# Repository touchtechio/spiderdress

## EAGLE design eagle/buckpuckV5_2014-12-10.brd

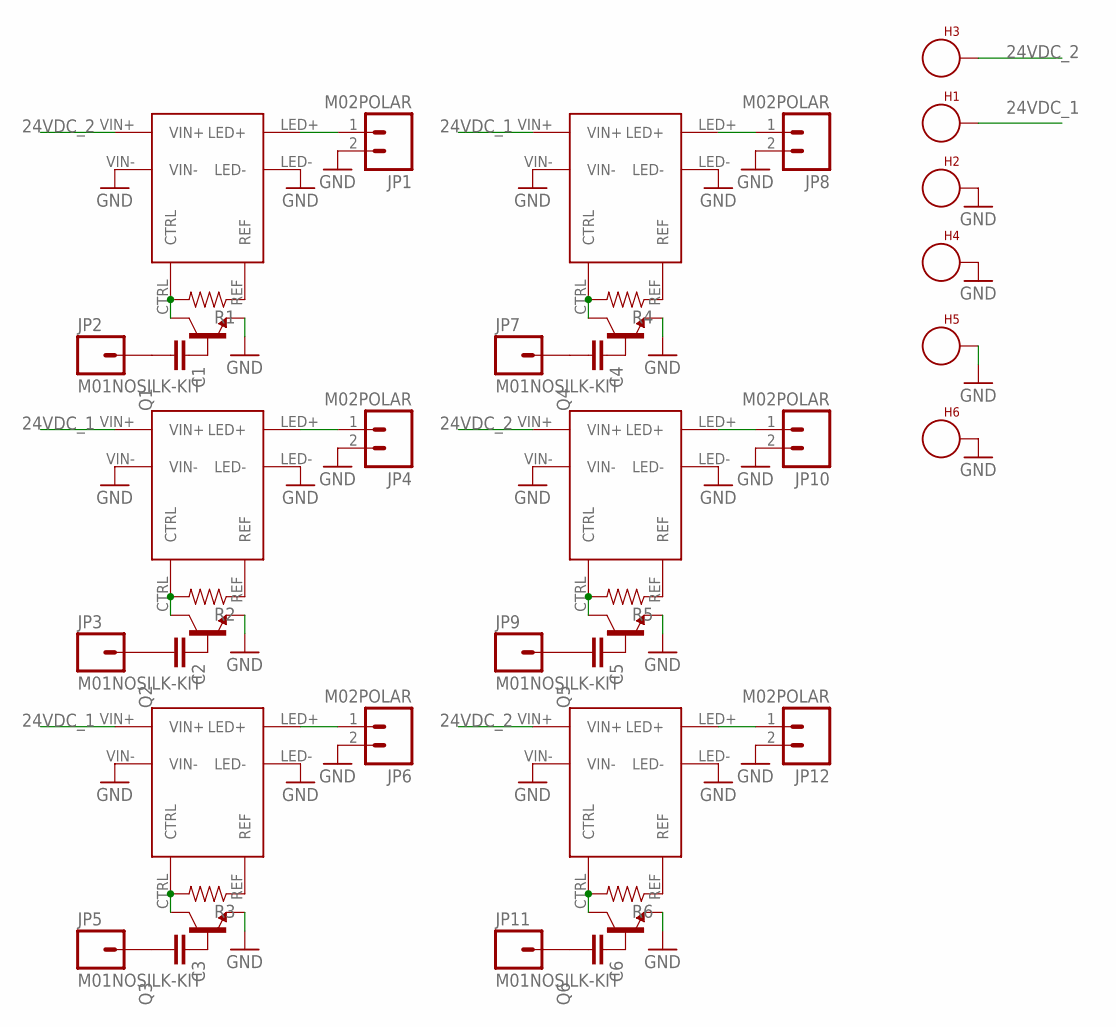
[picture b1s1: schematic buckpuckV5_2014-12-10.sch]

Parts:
C1, C2, C3, C4, C5, C6: CAPEZ; CAP-PTH-SMALLEZ
H1, H2, H3, H4, H5, H6: SEW_HOLE; SIMPLE_HOLE
JP1, JP4, JP6, JP8, JP10, JP12: M02POLAR; MOLEX-1X2
JP2, JP3, JP5, JP7, JP9, JP11: M01NOSILK-KIT; 1X01NS-KIT
Q1, Q2, Q3, Q4, Q5, Q6: TRANSISTOR_BJT_NPN-TO-92-EBC; TO-92
R1, R2, R3, R4, R5, R6: RESISTOREZ; AXIAL-0.3EZ
U$1, U$2, U$3, U$4, U$5, U$6: BUCKPUCK

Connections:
24VDC_1: H1.P$1, U$2.VIN+, U$3.VIN+, U$4.VIN+
24VDC_2: H3.P$1, U$1.VIN+, U$5.VIN+, U$6.VIN+
GND: H2.P$1, H4.P$1, H5.P$1, H6.P$1, JP1.2, JP4.2, JP6.2, JP8.2, JP10.2, JP12.2, Q1.1 (E), Q2.1 (E), Q3.1 (E), Q4.1 (E), Q5.1 (E), Q6.1 (E), U$1.LED-, U$1.VIN-, U$2.LED-, U$2.VIN-, U$3.LED-, U$3.VIN-, U$4.LED-, U$4.VIN-, U$5.LED-, U$5.VIN-, U$6.LED-, U$6.VIN-
unnamed: R1.P$1 (1), U$1.REF
unnamed: Q1.3 (C), R1.P$2 (2), U$1.CTRL
unnamed: C1.1, Q1.2 (B)
unnamed: R4.P$1 (1), U$4.REF
unnamed: JP1.1, U$1.LED+
unnamed: C1.2, JP2.1
unnamed: C2.1, Q2.2 (B)
unnamed: Q2.3 (C), R2.P$2 (2), U$2.CTRL
unnamed: C4.1, Q4.2 (B)
unnamed: C3.1, Q3.2 (B)
unnamed: JP4.1, U$2.LED+
unnamed: C2.2, JP3.1
unnamed: C6.1, Q6.2 (B)
unnamed: Q3.3 (C), R3.P$2 (2), U$3.CTRL
unnamed: Q4.3 (C), R4.P$2 (2), U$4.CTRL
unnamed: JP6.1, U$3.LED+
unnamed: C3.2, JP5.1
unnamed: R2.P$1 (1), U$2.REF
unnamed: C5.1, Q5.2 (B)
unnamed: R5.P$1 (1), U$5.REF
unnamed: R3.P$1 (1), U$3.REF
unnamed: JP8.1, U$4.LED+
unnamed: C4.2, JP7.1
unnamed: R6.P$1 (1), U$6.REF
unnamed: Q5.3 (C), R5.P$2 (2), U$5.CTRL
unnamed: JP10.1, U$5.LED+
unnamed: C5.2, JP9.1
unnamed: Q6.3 (C), R6.P$2 (2), U$6.CTRL
unnamed: JP12.1, U$6.LED+
unnamed: C6.2, JP11.1

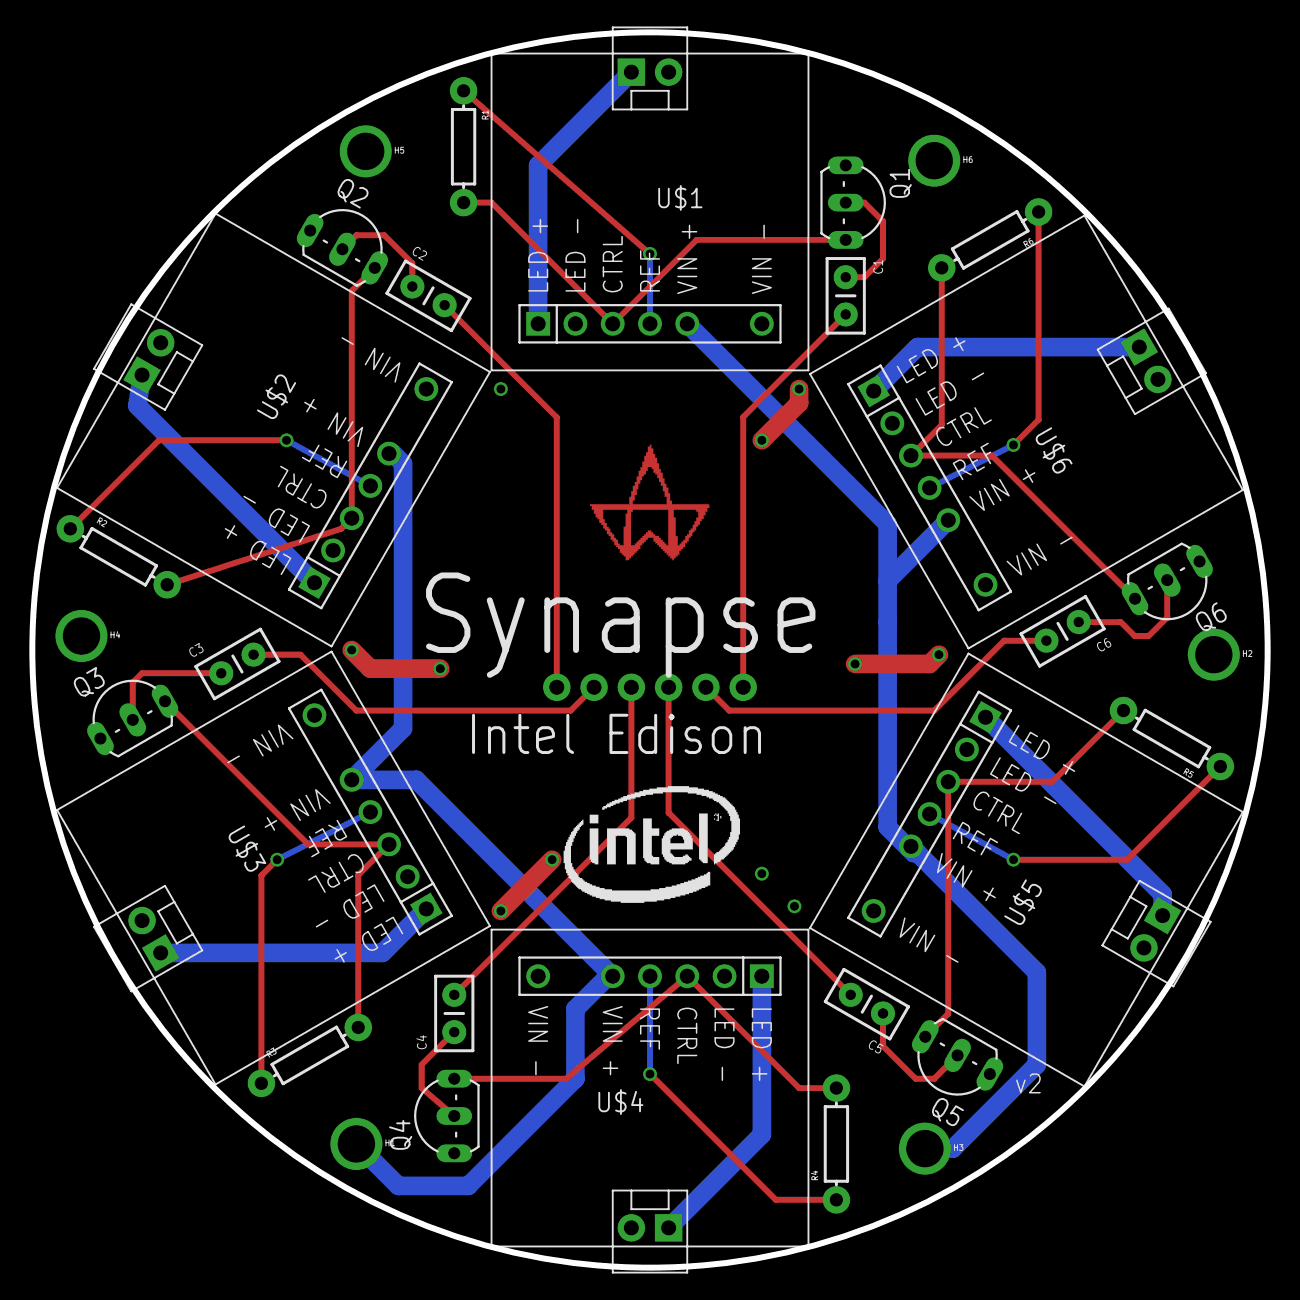
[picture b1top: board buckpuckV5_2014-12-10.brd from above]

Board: 2 copper layers, 84.2 x 84.2 mm, 44 parts (1 on the bottom side), 33 nets.

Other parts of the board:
U$7: NOUKLOGO3IN
U$8: NOUKLOGO300MIL_COPPER

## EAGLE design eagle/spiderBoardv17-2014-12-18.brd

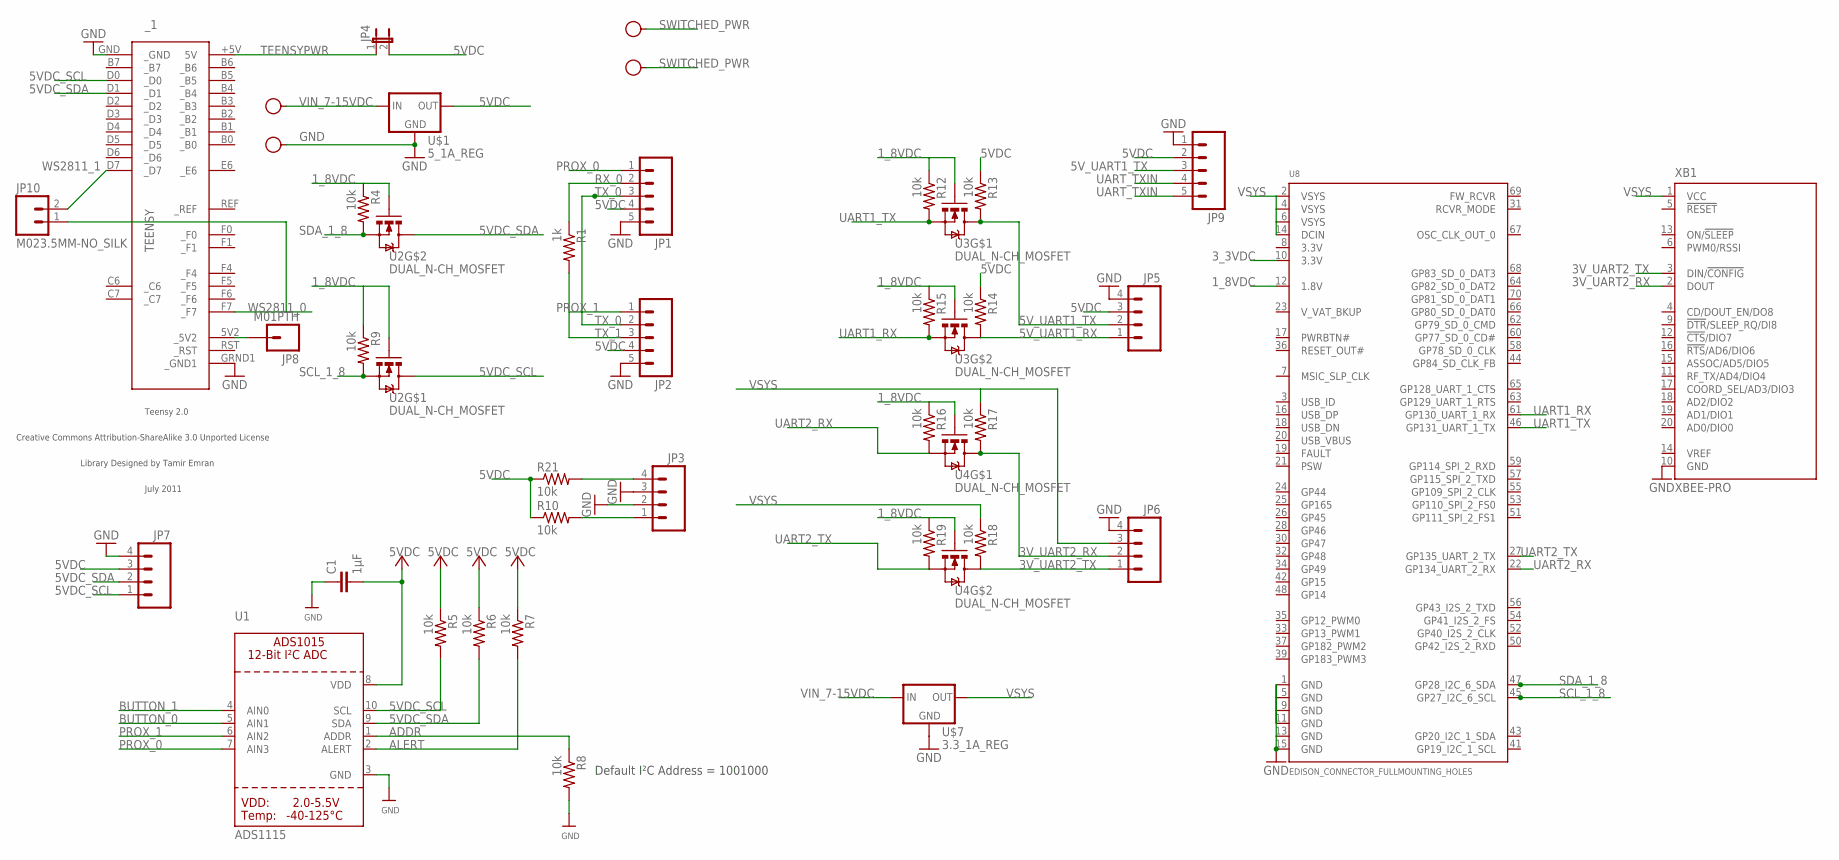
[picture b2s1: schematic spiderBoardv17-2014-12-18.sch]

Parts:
C1: 1µF; 0603-CAP
GND, GND15: SEW_HOLE-SMALL; SIMPLE_HOLE_SM
JP1, JP2, JP9: M05PTH; 1X05
JP3, JP5, JP6, JP7: M04PTH; 1X04
JP4: JUMPER-2SMD-NC; SJ_2S
JP8: M01PTH; 1X01
JP10: M023.5MM-NO_SILK; SCREWTERMINAL-3.5MM-2-NS
R1: 1k; 0603-RES
R4, R5, R6, R7, R8, R9, R10, R12, R13, R14, R15, R16, R17, R18, R19, R21: 10k; 0603-RES
U1: ADS1115; MSOP10
U2, U3, U4: DUAL_N-CH_MOSFET; SOT363_DUAL_N_MOSFET
U8: EDISON_CONNECTOR_FULLMOUNTING_HOLES; EDISON_DAUGHTER
U$1: 5_1A_REG; 1A_REG
U$7: 3.3_1A_REG; 1A_REG
VIN_7-15VDC, VIN_7-15VDC1: SEW_HOLE-SMALL; SIMPLE_HOLE_SM
XB1: XBEE-PRO
_1: TEENSY

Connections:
1_8VDC: R4.1, R9.1, R12.1, R15.1, R16.1, R19.1, U2.2 (G), U2.5 (G), U3.2 (G), U3.5 (G), U4.2 (G), U4.5 (G), U8.12 (1.8V)
3V_UART2_RX: JP6.2, R17.2, U4.3 (D), XB1.2 (DOUT)
3V_UART2_TX: JP6.1, R18.2, U4.6 (D), XB1.3 (DIN/!CONFIG)
3_3VDC: U8.10 (3.3V)
5VDC: C1.2, JP1.4, JP2.4, JP4.2, JP5.3, JP7.3, JP9.2, R5.1, R6.1, R7.1, R10.1, R13.1, R14.1, R21.1, U1.8 (VDD), U$1.OUT
5VDC_SCL: JP7.1, R5.2, U1.10 (SCL), U2.3 (D), _1.D0 (_D0)
5VDC_SDA: JP7.2, R6.2, U1.9 (SDA), U2.6 (D), _1.D1 (_D1)
5V_UART1_RX: JP5.1, R14.2, U3.6 (D)
5V_UART1_TX: JP5.2, JP9.3, R13.2, U3.3 (D)
ADDR: R8.1, U1.1 (ADDR)
ALERT: R7.2, U1.2 (ALERT)
BUTTON_0: JP3.4, R21.2, U1.5 (AIN1)
BUTTON_1: JP3.1, R10.2, U1.4 (AIN0)
GND: C1.1, GND.P$1, JP1.5, JP2.5, JP3.2, JP3.3, JP5.4, JP6.4, JP7.4, JP9.1, R8.2, U1.3 (GND), U8.1 (GND), U8.5 (GND), U8.9 (GND), U8.11 (GND), U8.13 (GND), U8.15 (GND), U$1.GND, U$7.GND, XB1.10 (GND), _1.GND (_GND), _1.GRND1 (_GND1)
PROX_0: JP1.1, U1.7 (AIN3)
PROX_1: JP2.1, U1.6 (AIN2)
RX_0: JP1.2, R1.1
SCL_1_8: R9.2, U2.4 (S), U8.45 (GP27_I2C_6_SCL)
SDA_1_8: R4.2, U2.1 (S), U8.47 (GP28_I2C_6_SDA)
SWITCHED_PWR: GND15.P$1, VIN_7-15VDC1.P$1
TEENSYPWR: JP4.1, JP8.1, _1.5V2 (_5V2), _1.+5V (5V)
TX_0: JP1.3, JP2.2
TX_1: JP2.3, R1.2
UART1_RX: R15.2, U3.1 (S), U8.61 (GP130_UART_1_RX)
UART1_TX: R12.2, U3.4 (S), U8.46 (GP131_UART_1_TX)
UART2_RX: R16.2, U4.4 (S), U8.22 (GP134_UART_2_RX)
UART2_TX: R19.2, U4.1 (S), U8.27 (GP135_UART_2_TX)
UART_TXIN: JP9.4, JP9.5
VIN_7-15VDC: U$1.IN, U$7.IN, VIN_7-15VDC.P$1
VSYS: JP6.3, R17.1, R18.1, U8.2 (VSYS), U8.4 (VSYS), U8.6 (VSYS), U8.14 (DCIN), U$7.OUT, XB1.1 (VCC)
WS2811_0: JP10.1, _1.F7 (_F7)
WS2811_1: JP10.2, _1.D7 (_D7)

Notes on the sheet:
Default I²C Address = 1001000

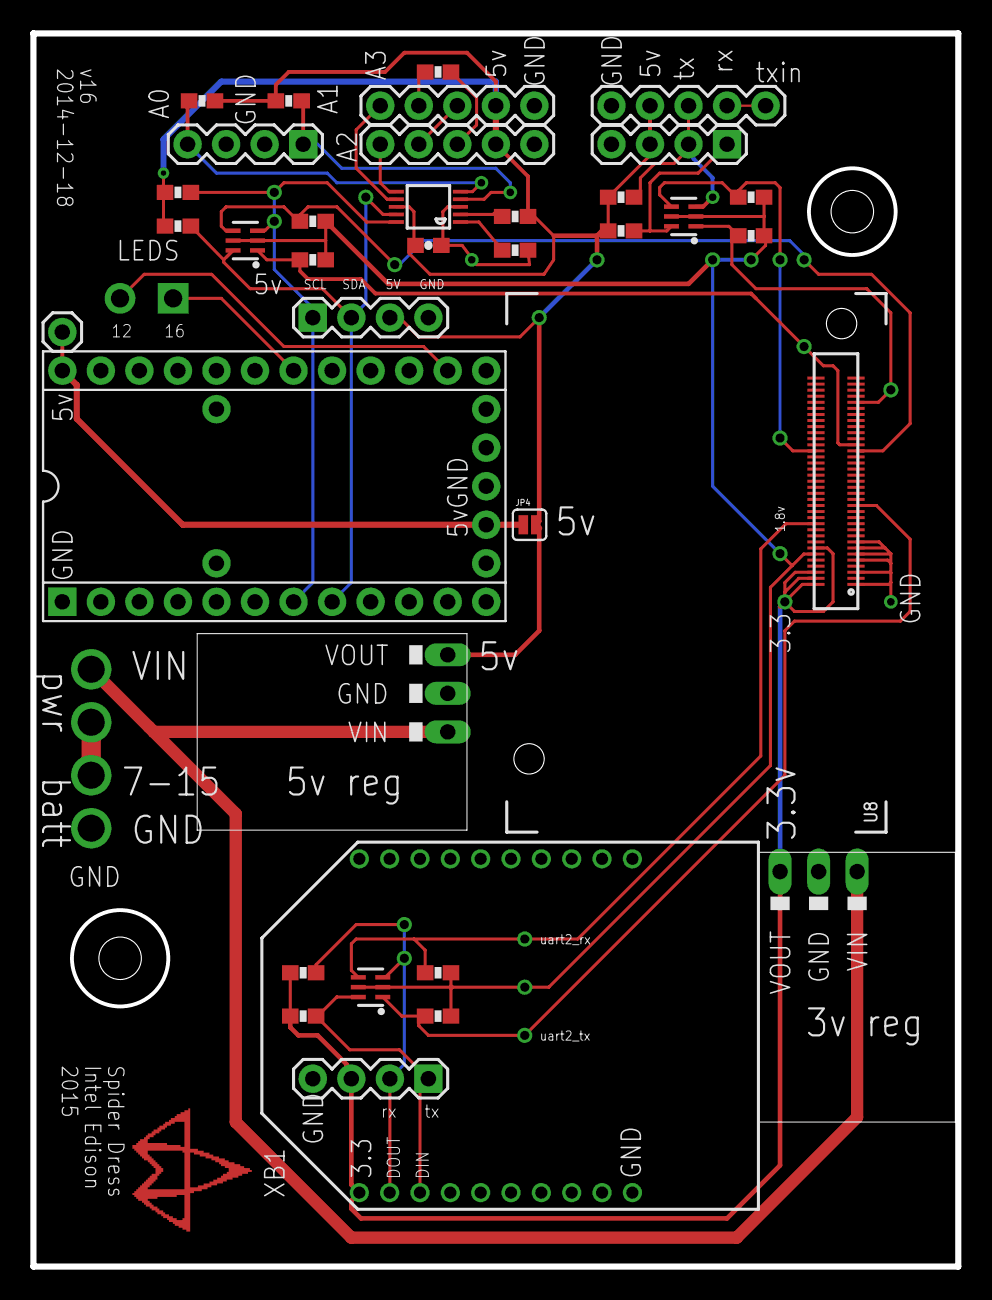
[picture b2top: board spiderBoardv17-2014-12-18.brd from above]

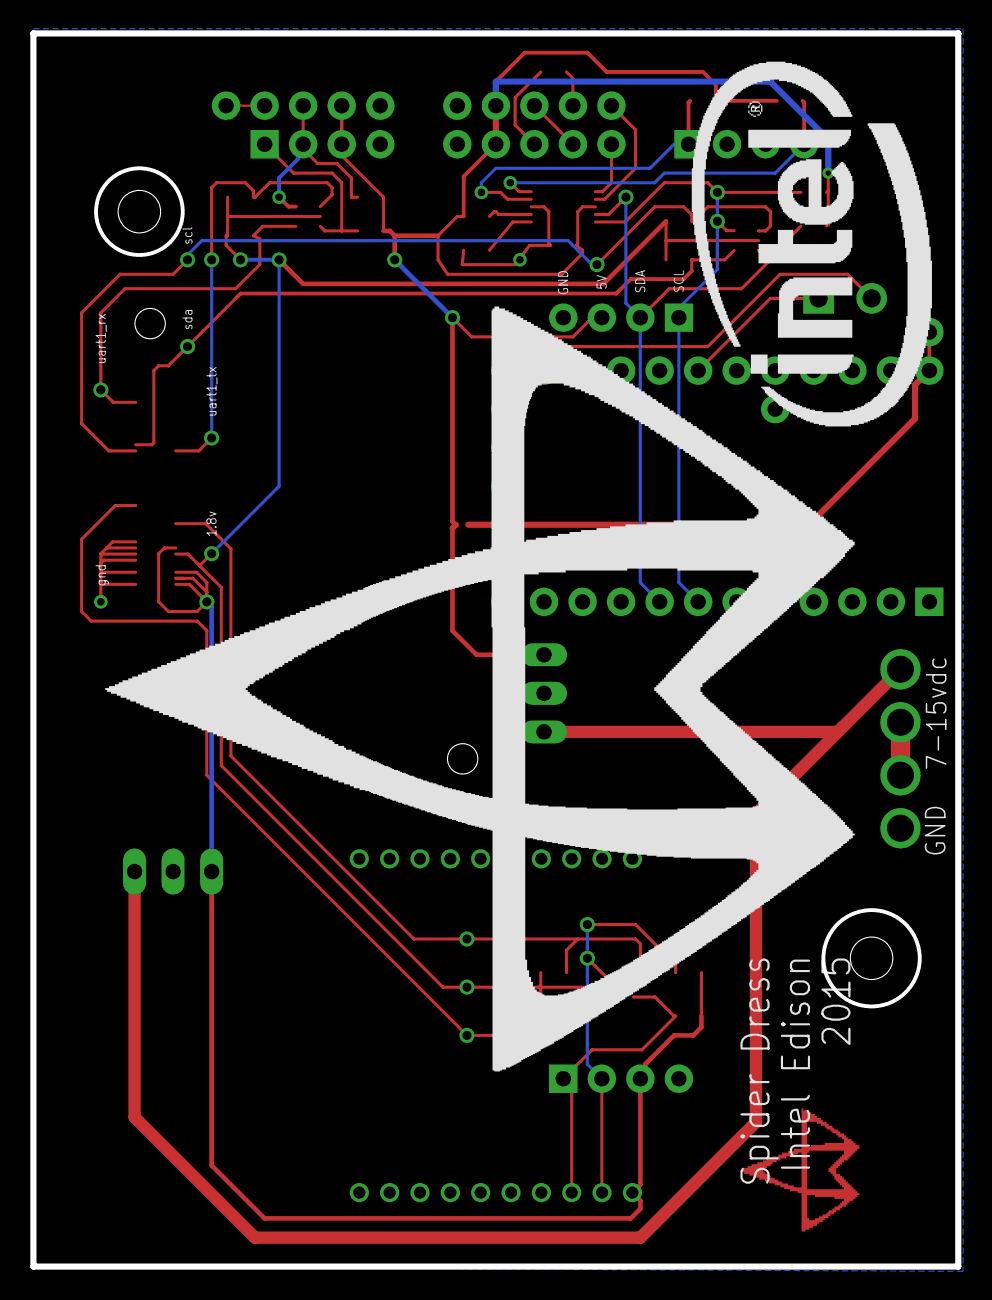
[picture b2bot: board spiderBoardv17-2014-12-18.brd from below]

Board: 2 copper layers, 61.0 x 81.3 mm, 44 parts (2 on the bottom side), 31 nets.

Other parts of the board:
U$9: NOUK-800
U$11: NOUKLOGO300MIL_COPPER
U$12: INTEL_1IN

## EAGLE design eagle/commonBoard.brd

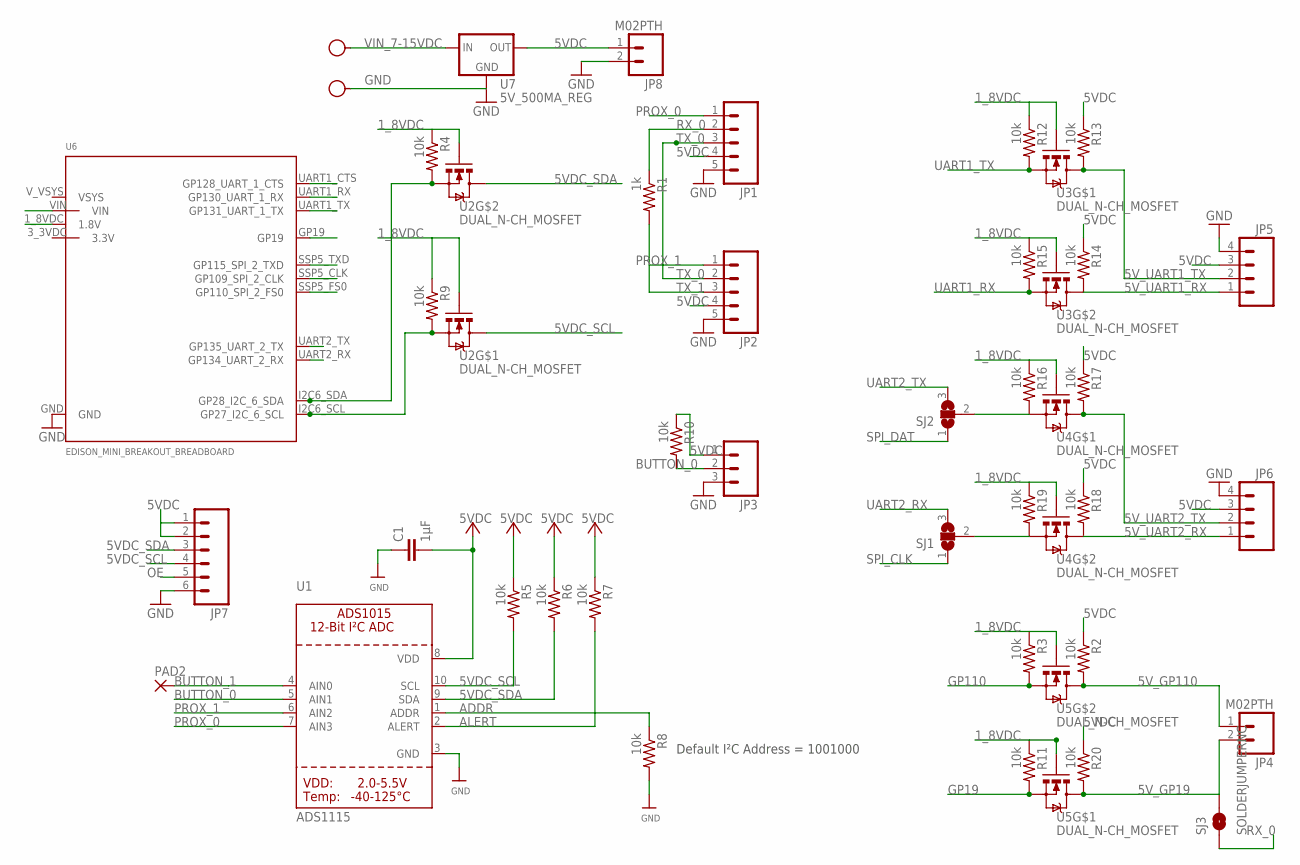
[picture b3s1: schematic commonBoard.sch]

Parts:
C1: 1µF; 0603-CAP
GND: SEW_HOLE-SMALL; SIMPLE_HOLE_SM
JP1, JP2: M05PTH; 1X05
JP3: M03PTH; 1X03
JP4, JP8: M02PTH; 1X02
JP5, JP6: M04PTH; 1X04
JP7: M06SIP; 1X06
PAD2: 2,15/1,0
R1: 1k; 0603-RES
R2, R3, R4, R5, R6, R7, R8, R9, R10, R11, R12, R13, R14, R15, R16, R17, R18, R19, R20: 10k; 0603-RES
SJ1, SJ2: SJ2W; SJ_2
SJ3: SOLDERJUMPERNC; SJ_2S
U1: ADS1115; MSOP10
U2, U3, U4, U5: DUAL_N-CH_MOSFET; SOT363_DUAL_N_MOSFET
U6: EDISON_MINI_BREAKOUT_BREADBOARD; EDISON_MINI_BREAK_BREADBOARD
U7: 5V_500MA_REG
VIN_7-15VDC: SEW_HOLE-SMALL; SIMPLE_HOLE_SM

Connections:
1_8VDC: R3.1, R4.1, R9.1, R11.1, R12.1, R15.1, R16.1, R19.1, U2.2 (G), U2.5 (G), U3.2 (G), U3.5 (G), U4.2 (G), U4.5 (G), U5.2 (G), U5.5 (G), U6.1_8VDC (1.8V)
5VDC: C1.2, JP1.4, JP2.4, JP3.1, JP5.3, JP6.3, JP7.1, JP7.2, JP8.1, R2.1, R5.1, R6.1, R7.1, R10.1, R13.1, R14.1, R17.1, R18.1, R20.1, U1.8 (VDD), U7.OUT
5VDC_SCL: JP7.4, R5.2, U1.10 (SCL), U2.3 (D)
5VDC_SDA: JP7.3, R6.2, U1.9 (SDA), U2.6 (D)
5V_GP19: JP4.2, R20.2, SJ3.2, U5.3 (D)
5V_GP110: JP4.1, R2.2, U5.6 (D)
5V_UART1_RX: JP5.1, R14.2, U3.6 (D)
5V_UART1_TX: JP5.2, R13.2, U3.3 (D)
5V_UART2_RX: JP6.1, R18.2, U4.6 (D)
5V_UART2_TX: JP6.2, R17.2, U4.3 (D)
ADDR: R8.1, U1.1 (ADDR)
ALERT: R7.2, U1.2 (ALERT)
BUTTON_0: JP3.2, R10.2, U1.5 (AIN1)
BUTTON_1: PAD2.1, U1.4 (AIN0)
GND: C1.1, GND.P$1, JP1.5, JP2.5, JP3.3, JP5.4, JP6.4, JP7.6, JP8.2, R8.2, U1.3 (GND), U6.GND, U7.GND
GP19: R11.2, U5.4 (S), U6.GP19
GP110: R3.2, U5.1 (S), U6.SSP5_FS0 (GP110_SPI_2_FS0)
unnamed: R9.2, U2.4 (S), U6.I2C6_SCL (GP27_I2C_6_SCL)
unnamed: R4.2, U2.1 (S), U6.I2C6_SDA (GP28_I2C_6_SDA)
OE: JP7.5
P1: R16.2, SJ2.2, U4.4 (S)
P2: R19.2, SJ1.2, U4.1 (S)
PROX_0: JP1.1, U1.7 (AIN3)
PROX_1: JP2.1, U1.6 (AIN2)
RX_0: JP1.2, R1.1, SJ3.1
SPI_CLK: SJ1.1, U6.SSP5_CLK (GP109_SPI_2_CLK)
SPI_DAT: SJ2.1, U6.SSP5_TXD (GP115_SPI_2_TXD)
TX_0: JP1.3, JP2.2
TX_1: JP2.3, R1.2
UART1_RX: R15.2, U3.1 (S), U6.UART1_RX (GP130_UART_1_RX)
UART1_TX: R12.2, U3.4 (S), U6.UART1_TX (GP131_UART_1_TX)
UART2_RX: SJ1.3, U6.UART2_RX (GP134_UART_2_RX)
UART2_TX: SJ2.3, U6.UART2_TX (GP135_UART_2_TX)
VIN_7-15VDC: U6.VIN, U7.IN, VIN_7-15VDC.P$1

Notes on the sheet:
Default I²C Address = 1001000

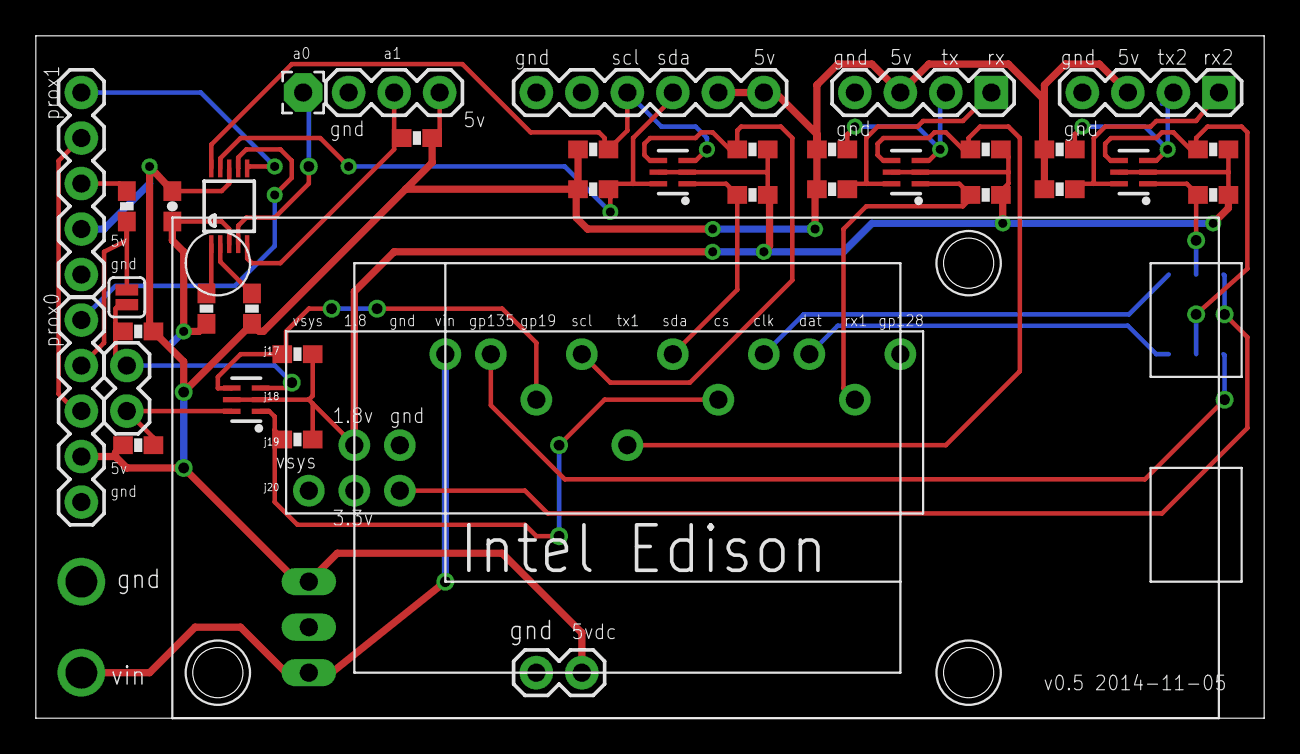
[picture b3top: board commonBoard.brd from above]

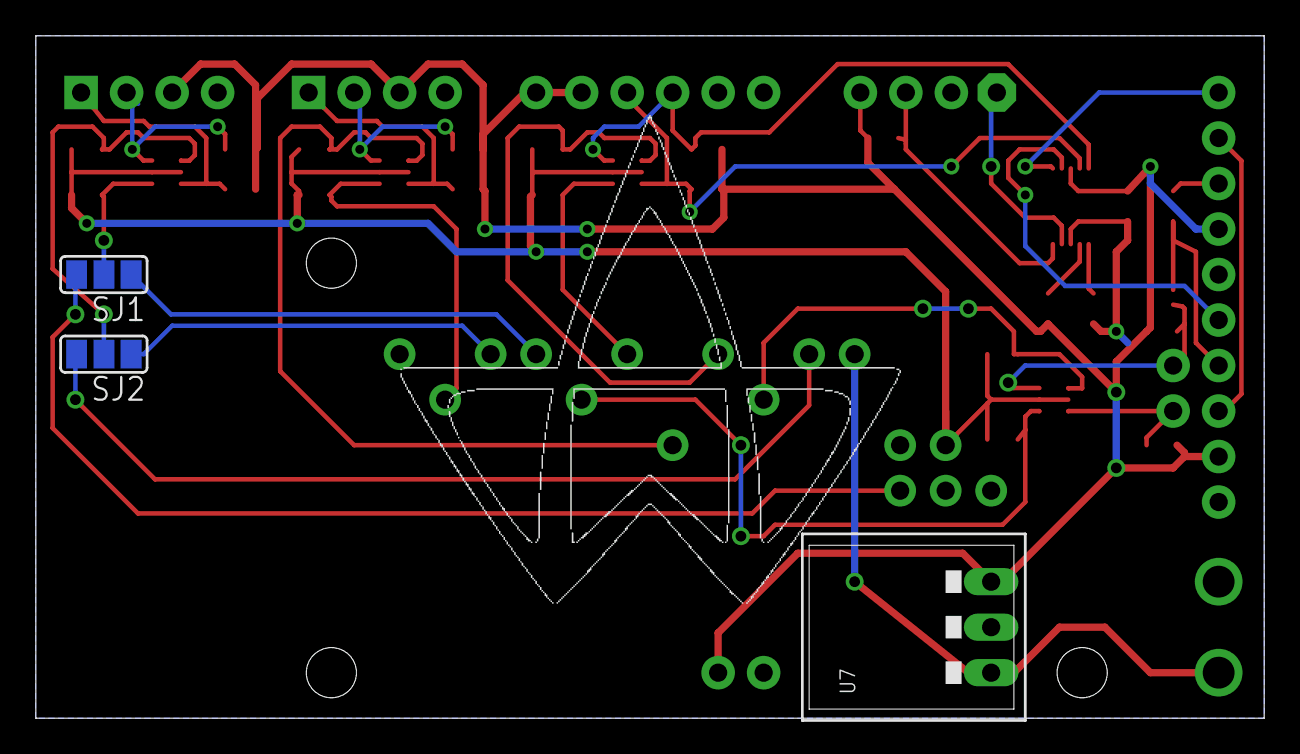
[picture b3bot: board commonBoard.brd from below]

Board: 2 copper layers, 68.6 x 38.1 mm, 42 parts (3 on the bottom side), 33 nets.

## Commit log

2014-10-14 initial add of servo scripts for testing servos
2014-10-24 initial add of basic functionality for controlling a servo using maestro
2014-10-24 modified init.sh to only enable gpios relavent to this dress
2014-10-24 adding command line interface for testing servos
2014-10-24 added ability to get servo position through interactive shell
2014-10-24 Set position function now uses Pololu protocol for Maestro.
2014-10-25 Add ability to drive multiple servos through single command in both maestro_controller.py and spider.py.
2014-11-05 Copy over edi2c and Maxbotix code from synapse.git:9853df3
2014-11-10 Remove pyc files.
2014-11-10 custom circuit board sent to fab : https://confluence.ndg.intel.com/display/SYN/Custom+PCB
2014-11-10 Folder structiore change and new bringup.
2014-11-10 Updated bringup and spider deployment added.
2014-11-10 making bringup mac friendly
2014-11-11 renaming and fixing mkdir -p tmp
2014-11-11 Make requests fully part of local repo
2014-11-11 cleaning up directory creation
2014-11-11 added hostap option and comments
2014-11-13 Changed set_position to use a different safe servo range. Removed MiniSSC protocol function.
2014-11-13 Fix documentation on set_position function.
2014-11-13 teensy and test client for i2c device to paint leds
2014-11-13 adding working copy of custom boards incase there is a revision
2014-11-13 added for completeness
2014-11-15 Set single servo command will now work with two chained Maestro controllers.
2014-11-17 Concurrent ADC support with test script.
2014-11-18 Set multiple targets working with chaining. Fixed bug in set single target with chaining.
2014-11-18 Include previously ignored files
2014-11-19 Allow processes to remain after being detached from remote session
    Issues: SPID-77
2014-11-19 Add screen ww46 package
2014-11-19 updated teensy script for our spider board (and moved)
2014-11-20 Implements servo script and leg abstractions.
2014-11-21 Run GPIO init scripts with absolute path
2014-11-21 Enable ad hoc networking on boot
2014-11-21 Add support for latest bringup with standardized image
    - Includes latest network configuration
    - Support for ssh over wifi by modifying systemd file
2014-11-21 Dotfiles
2014-11-21 moving password change
2014-11-21 removing some random broken copying
2014-11-21 adding my public key
2014-11-21 implements protocol for controlling teensy from edison
2014-11-21 rm extra teensy_tester.py
2014-11-22 adds first attempt at proximity teensy hook improves toggling between animations
2014-11-22 updated to support two strips (left and right)
2014-11-23 Add proximity reporting module
2014-11-23 Move test scripts into dedicated package
2014-11-23 Bug fixes set_accel, set_speed, set_position_multiple. Add script for park and extend for four legs.
2014-11-23 Add authorized key for Jason.
2014-11-23 enables toggling between animations and changing of brightness
2014-11-23 adds edison support for toggling animation and brightness
2014-11-23 improves live color toggling
2014-11-23 small color change
2014-11-23 adds glow and slow glow animation
2014-11-23 changes set_proximity_leds for phillip to test proximity adds set_count but it looks weird inside kidneys :)
2014-11-24 updated animations to activate from proximity
2014-11-24 same as last
2014-11-24 Bringup installer fixes and wifi support
2014-11-24 Proxemics support
2014-11-24 No debug logging
2014-11-24 Raw prox output for testing
2014-11-24 Extend pulse width range.
2014-11-24 Bug fixes for maestro controller, add function to determine movement state of servos, setup park and extend positions for all legs.
2014-11-24 Convert angles to pulse widths since angle is not a useful abstraction.
2014-11-24 Fix servos moving bug, add Monday servo script.
2014-11-24 Bug fix for running scripts.
2014-11-24 Add ability to run scripts from spider.py
2014-11-24 Add photoshoot functions and edit of photoshoot script.
2014-11-24 adds karli to authorized_keys
2014-12-04 disco bug fix attempt
2014-12-04 Add new publish-subscribe system intended for sensor/servo/LED integration.
2014-12-04 fixes disco and io write errors Please enter the commit message for your changes. Lines starting
2014-12-08 Clean up maestro_controller code to better adhere to PEP8.
2014-12-08 adding to test leds with spider teensy
2014-12-09 Reject bad prox readings
2014-12-09 adding for dipka
2014-12-10 Make request for user input more noticeable
2014-12-12 Initial implementation of new animation system. Needs to be tested.
2014-12-12 Documentation and code style cleanup.
2014-12-13 Fix "default" script, an initialization fix for starting leg position.
2014-12-16 Only do program step timing when duration specified
2014-12-16 Don't exit when resetting PWM
2014-12-16 Proper signal handling
2014-12-18 Fix animation bug, add servo values for several new positions.
2014-12-18 Animate will now take specific times for both safe route and final position.
2014-12-18 Fix spider.py to conform to new animate function.
2014-12-18 Adds ability to run "animations".
2014-12-19 New animations added, changes to the way position reached is determined in the animation system. Changes to the command line program to reflect MaestroController changes.
2014-12-19 Adds ability to test maestro get position from command line script.
2014-12-19 Work around for some maestro read issues.
2014-12-20 Proximity measurement tweaks
2014-12-20 Asynchronous proxemic space monitoring
2014-12-20 Adds one new animation. Change to the way the get position function works during animation.
2014-12-22 Distance callback
2014-12-22 Distance callback on public function
2014-12-23 Adds animations zones, read positions from file, get errors over UART, bug in get position code fix.
2014-12-23 Positions for "dress a" added to file. Dress A is the first spider dress that was built.
2014-12-23 Initial integration commit for prox+servos.
2014-12-23 Simple animation based on proximity. Adds teensy+prox interaction.
2014-12-23 Adds ability to disable maestro pulse to all servos.
2014-12-24 Initial respiration integration.
2014-12-24 Tuning of animation code.
2014-12-24 Animation state based on proximity changes.
2014-12-24 Increase threshold value for respiration trigger.
2014-12-24 Sticky prox space
2014-12-24 Sticky prox space in main function
2014-12-24 Sticky prox space fix.
2014-12-24 Fix to personal animation space.
2014-12-24 Tweaks to animation/prox/respiration interaction. Fix push_away position values.
2014-12-27 Adds button support for two separate CES modes, one with all interaction, the other with only slow breathe. Old spider.py now spider_command, with new spider.py intended to be run and not interacted 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
2014-12-29 Remove point position. Add positions for dress b.
2014-12-29 Amend dress b positions.
2014-12-29 Tweak servo positions for dress b.
2014-12-29 spider_command takes a leg file in it's command line arguments.
2014-12-30 More tweaks to dress b positions.
2014-12-30 Tweaks to some animations.
2014-12-30 Fixes bug in button press code, allowing modes to change correctly.
2014-12-30 defaults color to pure whilte 255,255,180
2015-01-04 New servo requires new position data.
2015-01-04 Add new button mode, fix spider_command set multiple servos.
2015-01-04 Clear errors when MaestroController starts.
2015-01-04 Initial addition of spider.py to init script.
2015-01-05 Fix init script spider.py startup problems.
2015-01-05 Tweaks to jugendstil animation.
2015-01-05 Respiration will now not break the interaction if it isn't plugged in.
2015-01-06 Respiration calibration for Whitney.
2015-01-06 Changes the way the modes flow when button is pressed.
2015-01-07 Tweaks to animations for CES floor.
2015-01-08 New servo positions for replaced servo.
2015-01-09 New positions for 3 new servos.
2015-01-20 adding for jason's review
2015-01-20 added file writing
2015-01-20 added filename as arg with default
2015-01-22 hacked up the maestro init for use on mac for testing and direct servo calibration. //todo: better encapsulation
2015-01-22 now processor depends on maestro and serial connections // todo: break dependency out and import tty on edison
2015-01-22 ported back to edison
2015-01-24 made backward compatible
2015-01-24 added deafulting to park
2015-01-24 rename
2015-01-24 renamed
2015-01-24 adding shell board
2015-01-24 latest buckpuck boards

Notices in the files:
parts and their libraries:
SparkFun-Capacitors: Licensing: Creative Commons ShareAlike 4.0 International - https://creativecommons.org/licenses/by-sa/4.0
SparkFun-Passives: Licensing: CC v3.0 Share-Alike You are welcome to use this library for commercial purposes.
